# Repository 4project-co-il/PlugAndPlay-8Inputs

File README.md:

# PlugAndPlay: Input module with 8 screw terminals
This is the repository with the files for PlugAndPlay input module with 8 screw terminals

That module has 8 screw terminals, connected to the PnP interrupt line via TCAL9538PWR multiplexer.

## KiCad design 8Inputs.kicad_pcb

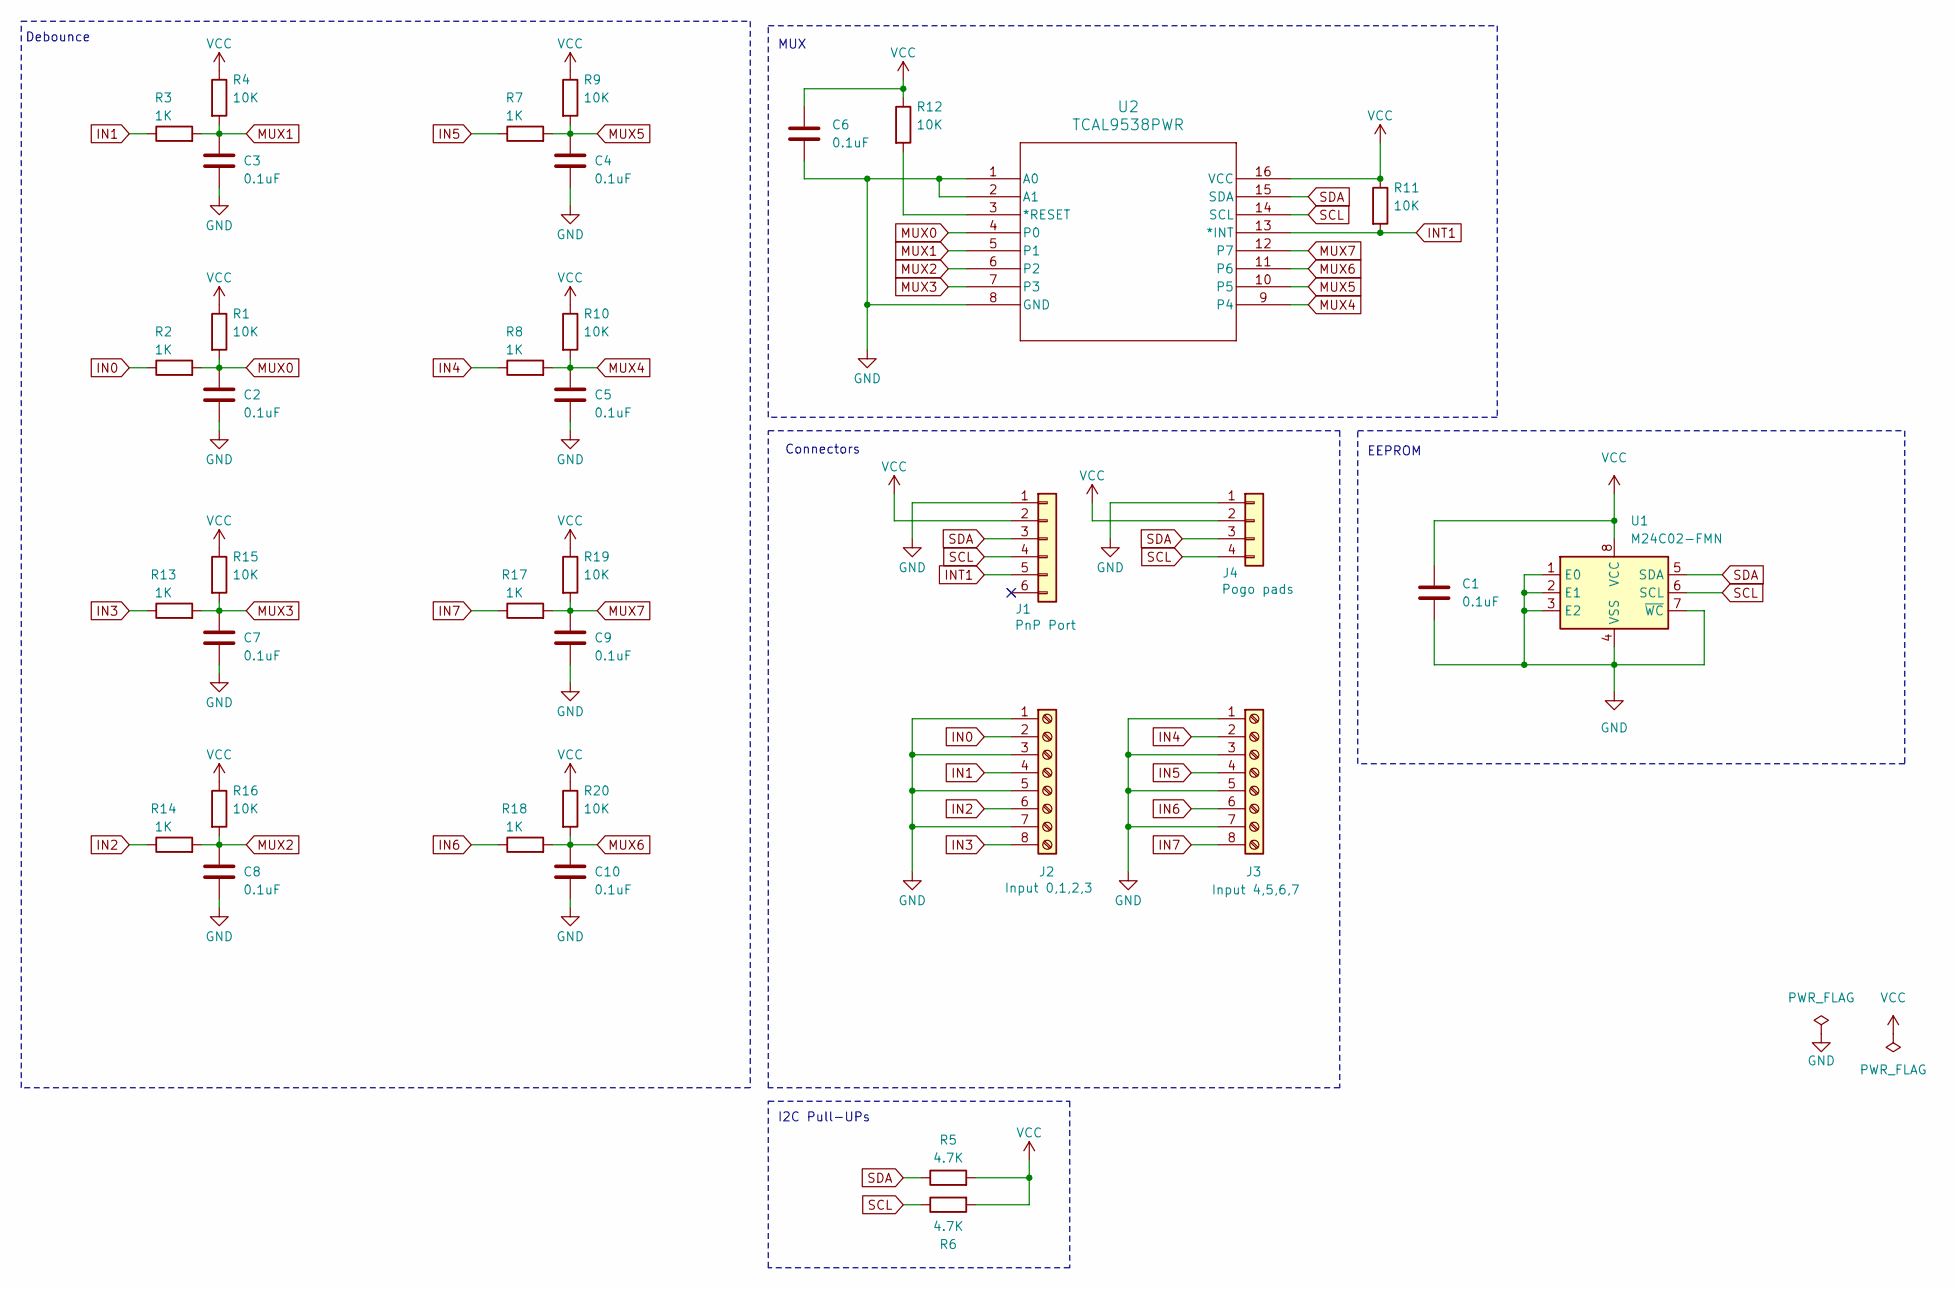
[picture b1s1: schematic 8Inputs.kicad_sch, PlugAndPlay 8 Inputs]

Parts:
C1, C2, C3, C4, C5, C6, C7, C8, C9, C10: 0.1uF; C_0603_1608Metric; MPN C14663
J1: JST_SH_SM06B-SRSS-TB_1x06-1MP_P1.00mm_Horizontal; MPN C7430448
J2: Input 0,1,2,3; TerminalBlock_4Ucon_1x08_P3.50mm_Horizontal
J3: Input 4,5,6,7; TerminalBlock_4Ucon_1x08_P3.50mm_Horizontal
J4: Conn_01x04; PogoPinsPads_1x04_P2.5mm
R1, R4, R9, R10, R11, R12, R15, R16, R19, R20: 10K; R_0603_1608Metric; MPN C25804
R2, R3, R7, R8, R13, R14, R17, R18: 1K; R_0603_1608Metric; MPN C21190
R5, R6: 4.7K; R_0603_1608Metric; MPN C4190
U1: M24C02-FMN; SOIC-8_3.9x4.9mm_P1.27mm; MPN C114502
U2: TCAL9538PWR; TSSOP-16_4.4x5mm_P0.65mm

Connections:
GND: C1.2, C2.2, C3.2, C4.2, C5.2, C6.2, C7.2, C8.2, C9.2, C10.2, J1.1, J2.1, J2.3, J2.5, J2.7, J3.1, J3.3, J3.5, J3.7, J4.1, U1.1 (E0), U1.2 (E1), U1.3 (E2), U1.4 (VSS), U1.7 (~WC), U2.1 (A0), U2.2 (A1), U2.8 (GND)
IN0: J2.2, R2.1
IN1: J2.4, R3.1
IN2: J2.6, R14.1
IN3: J2.8, R13.1
IN4: J3.2, R8.1
IN5: J3.4, R7.1
IN6: J3.6, R18.1
IN7: J3.8, R17.1
INT1: J1.5, R11.2, U2.13 (*INT)
MUX0: C2.1, R1.2, R2.2, U2.4 (P0)
MUX1: C3.1, R3.2, R4.2, U2.5 (P1)
MUX2: C8.1, R14.2, R16.2, U2.6 (P2)
MUX3: C7.1, R13.2, R15.2, U2.7 (P3)
MUX4: C5.1, R8.2, R10.2, U2.9 (P4)
MUX5: C4.1, R7.2, R9.2, U2.10 (P5)
MUX6: C10.1, R18.2, R20.2, U2.11 (P6)
MUX7: C9.1, R17.2, R19.2, U2.12 (P7)
unnamed: R12.2, U2.3 (*RESET)
SCL: J1.4, J4.4, R6.1, U1.6 (SCL), U2.14 (SCL)
SDA: J1.3, J4.3, R5.1, U1.5 (SDA), U2.15 (SDA)
VCC: C1.1, C6.1, J1.2, J4.2, R1.1, R4.1, R5.2, R6.2, R9.1, R10.1, R11.1, R12.1, R15.1, R16.1, R19.1, R20.1, U1.8 (VCC), U2.16 (VCC)

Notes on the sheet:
EEPROM
MUX
Connectors
I2C Pull-UPs
Debounce

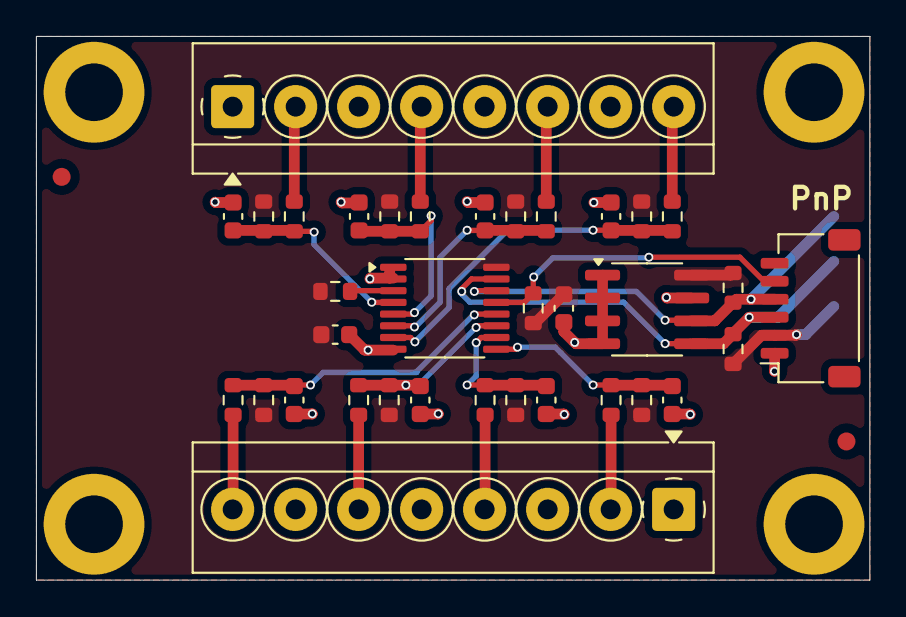
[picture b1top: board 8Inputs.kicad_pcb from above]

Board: 2 copper layers, 46.3 x 30.2 mm, 36 parts (1 on the bottom side), 22 nets.
